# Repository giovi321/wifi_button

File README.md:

This is a cheap, customizable, WiFi-enabled, battery-operated, ultra-low power consumption touch button with no moving parts that relies on ESPHome and is designed to be used with Home Assistant.
It is designed to be long-lasting both in terms of durability and battery life and easy to build & operate.

Did you like the project?

# License
The content of this repository is licensed under the [WTFPL](http://www.wtfpl.net/).

```
Copyright © 2023 giovi321
This work is free. You can redistribute it and/or modify it under the
terms of the Do What The Fuck You Want To Public License, Version 2,
as published by Sam Hocevar. See the LICENSE file for more details.
```

# Features
- Minimalist design (i.e., no moving parts, fit with the design of my house)
- No mechanical button (i.e., I just want to slap my hand on a big enough device while I'm laying on my bed)
- USB type C charging port (i.e., charge it with my laptop charger)
- At least one year of battery (i.e., charge it once a year and forget about it)
- WiFi enabled, I don't want to configure also BLE on my Home Assistant device
- Battery status (i.e., get a notification on Home Assistant when it needs to be charged)
- As cheap as possible (this makes z-wave not an option)

# Shopping list
The items in the following links are just proposals, you can obviously source the exact same products wherever you prefer.
Prices include shipping to Europe.
- [Wemos D1 Mini](https://www.aliexpress.com/item/32651747570.html) [3.33€]
- [USB plug](https://www.aliexpress.com/item/1005005476223469.html) [1.77€]
- [USB type C charging circuit](https://www.aliexpress.com/item/1005005227218470.html) [1.87€]
- [Battery 2000mAh](https://www.aliexpress.com/item/1005002919536938.html) [5.44€]
- [Photocoupler TLP570](https://www.aliexpress.com/item/1005004627959174.html) [2.14€]
- [Capacitive touch sensor](https://www.aliexpress.com/item/32874585710.html) [0.60€]
- [180k ohm resistor](https://aliexpress.com/item/1005004562905294.html) [2.55€]
- [Autotapping screws M2.6 x 5mm](https://www.aliexpress.com/item/1005003330377202.html)  [1.30€]
- Optional: [Screw connector for PCB](https://www.aliexpress.com/item/4001283309384.html), if you want you can solder the battery directly to the PCB/breadboard [1.90€]
- Optional: [PCB pin header strip](https://www.aliexpress.com/item/1005003541838313.html), if you want you can solder the cables that connect the touch sensor directly to the PCB/breadboard [1.17€]
- Optional: [PCB mounted micro switch 90°](https://www.aliexpress.com/item/1005005338134247.html), if you don't require the switch, you can place a jumper in place of the switch in the board [3.15€]

- Options for PCB:
  - Breadbord (make your own design) [c. 3€]
  - PCB I have designed
    - Available for purchase [here](https://www.buymeacoffee.com/giovi321/e/147823) [15€ cad., 3€ for additional boards]
    - Print your own on [allpcb](https://www.allpcb.com/?Mb_InviteId=60399) [c. 30€ excl. import taxes], see the Gerber files in the repository
 - 3D printed case (see the .stl files in this repository)
   -  Print it yourself [c. 3€]
   -  Print it on xometry.eu [c. 36€]

# Resources
- Circuit schematic - see the files in the "PCB" folder of the repository

- 3D case - see the files in the "3D stl" folder of the repository and check the README.md file in that folder

# How does it work
- The USB type C connector makes the device modern and easy to charge, but feel free to use any other type of connector
- The charger module keeps the battery charged and you safe from fire hazards, it is simply plug and play
- The device is based on the Wemos D1 Mini (I'm using a cheap clone, even though a branded one would be better for lower energy consumption) and ESPHome because they are very easy to use; certainly there are more energy efficient solutions
- We need a voltage sensor connected to one analog input of the Wemos D1 Mini in order to read the battery status and receive a notification on Home Assistant when it is about to die. To do this, we take advantage of the integrated voltage divider of the pin A0 of the Wemos D1 Mini, which can support up to 3.3 volts input. Since we are providing a 5 volts input, we need to add a 180kohm resistor
- In order to keep energy consumption low, we need to keep the Wemos D1 Mini in a deep-sleep state
	- however, in deep sleep state the Wemos D1 Mini won't be able to read an input offered by the touch sensor
	- therefore, I have opted to use the touch sensor to wake up the Wemos D1 Mini that will go in deep-sleep automatically every 10 seconds
	- the Wemos D1 Mini will be configured to send two mqtt messages whenever it wakes up:
		- one message with the battery voltage
		- one message with "hey somebody touched the touch sensor"
- 3.7v battery is the way to go to power the Wemos D1 Mini, and 2000 mAh fits the small design of the case; feel free to use a different amperage battery. It provides up to 1.5 years of uptime on a single charge (it can vary, see the dedicated section of this file)
   - I haven't tested it, but from my research online the power consumption of different versions of Wemos D1 Mini in deep-sleep mode powered from the 5v input (which is less efficient because there is a voltage regulator in the middle) can vary depending on the manufacturer (see table below)
   - Assuming we are unlucky and got the worse energy-performing Wemos D1 Mini, the average consumption is 69.47mA, giving it a life of almost 399 days (the calculation steps are available below). If we take into consideration the best case scenario, that is 78µA consumption, the battery would last almost 3x: 1,068 days
   - We are not taking into consideration the power consumption of the touch sensor, phototransistor and voltage sensor. The first two components have a very small consumption as it peaks mostly when you activate the touch sensor. For the voltage sensor I couldn't find anything online. In any case, even assuming an absurde value of 15% increase in power consumption, it's still a decent number of days.
   - I don't think I need to say that: i) these values are purely theorethical, the nominal rating of the battery does not equal its empirical performance; ii) the amount of times you will use the button will influence the duration of the battery
   - Pro tip: if you desolder the LED that is installed on the touch sensor, you save some precious µA. However I haven't tried it and I don't know if it would affect the touch sensor functionality
```
Wemos D1 Mini power consumption table
          | WEMOS D1 MINI CLONE | WEMOS D1 MINI LOLIN | WEMOS D1 MINI WAVGAT |
|:-------:|:-------------------:|:-------------------:|:--------------------:|
| Minimum |        144 µA       |         75µA        |        206 µA        |
| Maximum |        147 µA       |         80µA        |        214 µA        |
| Average |        156 µA       |         78µA        |        209 µA        |

Source: https://programarfacil.com/esp8266/esp8266-deep-sleep-nodemcu-wemos-d1-mini/
```
```
Battery life calculation steps
To calculate the approximate duration of a battery with a given load, you can use the formula:
	Battery Life (in hours) = Battery Capacity (in mAh) / (Load Current (in µA) / 1000)
The battery capacity is 2000 mAh and the load current is 209 µA. Plugging these values into the formula:
	Battery Life = 2000 mAh / (209 µA / 1000) ≈ 9569.38 hours
	Battery Life in days = 9569.38 hours / 24 ≈ 398.72 days
```
- As mentioned earlier, a touch sensor does not provide an analog output. To use it, you need to interface it with a microcontroller like the Wemos D1 Mini, or in our case, to minimize energy consumption, we can opt to use a phototransistor
- The phototransistor is a straightforward electronic component with two inputs and two outputs:
	- the two inputs are the anode (+) and cathode (-) of a LED integrated in the package of the chip
	- the two outputs are the Emitter and Collector of the transistor, to put it simple those two pins allow current to flow between the two pins when the phototransistor is "activated"
- When the touch sensor is activated with your finger, it provides the phototransistor with current, enough to light the internal LED of the phototransistor, therefore allowing current to pass between the emitter and the collector of the transistor
  - When the current flows between the Emitter and the Collector, we are simply shorting the RST and GND pins of the Wemos D1 Mini, therefore waking it up

# Building process
## Hardware
### Electronics
Just follow the schematics provided in the Resources chapter of the readme to build your own breadbord, otherwise simply solder the components on the PCB ordered either from me or another producer.

### Case
The assembly is extremly simple:
- Using a flat cutter, trim the pins protruding from the PCB of the touch sensor in order to make in more flat and therefore make sure it sticks closely to the top of the case
- Hot glue the touch sensor to the top flat part of the dome (inside the dome, obviously) - the sensor can feel touch also through a thin layer of non conductive material (the layer of the top of the dome is 1mm thick)
- Insert the USB type C connector from the bottom of the bottom plate and glue it with cyanoacrylate glue
- Solder the connector to the battery charger module and plug the battery
- Place the PCB on the stands of the bottom part of the case (if you wish, you can melt with a hot flat-head screwdriver the plastic to keep the PCB in place)
- Close the dome and use four M2.6 screws to secure it

## Software
### Install ESPHome
There are three ways to install ESPHome:
- If you have hass.io (the official home-assistant OS), follow [this guide](https://www.home-assistant.io/integrations/esphome/)
- If you are running any other version of home-assistant such as a venv or docker you have the following two options:
  - Use docker, following [this guide](https://esphome.io/guides/installing_esphome.html)
  - Install it in a python venv following the simple steps below or follow [this guide](https://esphome.io/guides/installing_esphome.html)
```
python3 -m venv esphome
source esphome/bin/activate
pip3 install esphome
```
Check that ESPHome has been installed correctly:
```
esphome version
```
If you're not running hass.io, you can install ESPHome dashboard by following the steps below or [this guide](https://esphome.io/guides/getting_started_command_line.html?highlight=dashboard+install#bonus-esphome-dashboard)

```esphome dashboard config/
pip install tornado esptool
```
Test the installation:`esphome dashboard config/`
Create a new systemd service to run the dashboard automatically by issuing (as root) `nano /etc/systemd/system/esphome.service`.
Now put this in the file, close and save it.
```
[Unit]
Description=ESPHome Dashboard
After=network-online.target

[Service]
Type=simple
ExecStart=/root/esphome/bin/esphome config/ dashboard
Restart=on-failure
RestartSec=5s

[Install]
WantedBy=multi-user.target
```
Issue the following:
```
systemctl --system daemon-reload
systemctl enable esphome.service
```
Then check if the service is running by issuing `service esphome status`.

### ESPHome code
ATTENTION: remember to switch off the main circuit board (or unplug the battery, if you didn't include the switch) before connecting the Wemos D1 Mini to the computer via USB!

```
mqtt:
  broker: 192.168.1.100
  username: yourmqttusername
  password: yourmqttpassword
  birth_message:
    topic: esphome/bedside_light_switch_1
    payload: "on"

deep_sleep:
  run_duration: 10s

sensor:
  - platform: adc
    pin: A0
    name: "Bedside light switch 1 battery"
    id: battery_voltage_12f
    filters:
      - multiply: 4.511904762
    accuracy_decimals: 3
```
ATTENTION: to calculate the 4.511904762 value (second line from the bottom of the code snippet for ESPHome) you need to:
- measure the battery voltage with a multimeter when the device is running (i.e., not in deep-sleep mode)
- set the value to 1 like this: `multiply: 1`
- check what value is reported on home assistant from the device
- do a very simple proportion:
```
a:b=c:x
b*c/a=x
a=the reported voltage from home assistant
b=the multiplier you set (1)
c=the voltage measured by your multimeter

0.840:1=3.79:x
1*3.79/0.840=4.511904762
```
So with those numbers (they might vary depending on the Wemos D1 Mini brand and the battery type) the multiplier we need to set is 4.511904762.

### Home Assistant code
Add the sensor for the battery to convert voltage to percentage (edit configuration.yaml)
Remember to change the name of the sensor `sensor.bedside_light_button_1_bedside_light_button_1_battery` to your sensor's name.
The values shown in this code snipped apply to 3.7v lithium batteries.
```
sensor:
  - platform: template
    sensors:
      bedside_light_button_1_battery_percentage:
        friendly_name: "Bedside light button 1 battery percentage"
        device_class: battery
        unit_of_measurement: "%"
        value_template: >
          {% set voltage = states('sensor.bedside_light_button_1_bedside_light_button_1_battery')|float %}
          {% if voltage < 2.64 %}
            0
          {% else %}
            {% set range_voltage = 3.85 - 2.64 %}
            {% set range_percentage = 100 %}
            {% set battery_percentage = ((voltage - 2.64) / range_voltage) * range_percentage %}
            {{ battery_percentage | round(0) }}
          {% endif %}
```

Add the automation to trigger the light when you press the button (edit automations.yaml):
```
- alias: bedside_light_switch_1
  description: 'Turn on bedside table lamp on button touch'
  trigger:
  - platform: mqtt
    topic: esphome/bedside_light_switch_1
    payload: 'on'
  mode: single
```

Add  a notification on low battery (edit automations.yaml):
```
- alias: Bedside light 1 low battery
  description: 'Send notification if bedside light button battery is below 10%'
  trigger:
  - platform: numeric_state
    entity_id: sensor.bedside_light_button_1_battery
    below: 10
  action:
  - service: notify.persistent_notification
    data:
      message: The battery of bedside light 1 is low. Please charge.
      title: Bedside light 1 low battery
  mode: single
```

# The outcome
The final result:
[Piucture TBU]

The bare metal device:

The early prototype:

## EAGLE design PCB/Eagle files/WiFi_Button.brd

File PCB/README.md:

In this folder you can find all the files needed to print the PCB.
If you need to print from [allpcb](https://www.allpcb.com/?Mb_InviteId=60399), simply upload the file WiFi_Button.zip.

## Schematic

## PCB layout

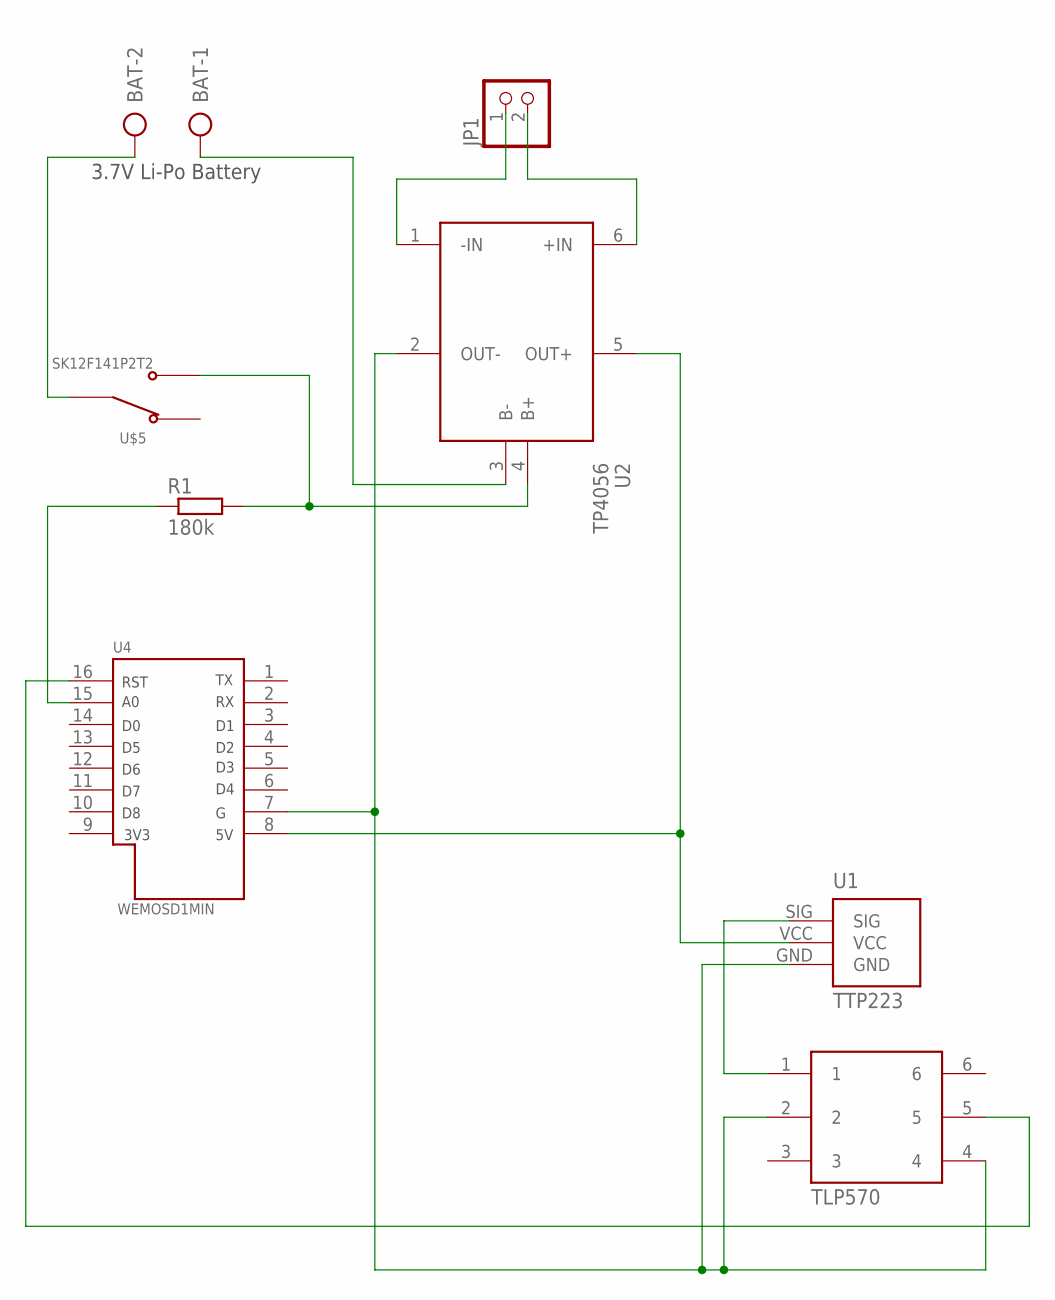
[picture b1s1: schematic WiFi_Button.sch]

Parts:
BAT: AK500/2
JP1: PINHD-1X2; 1X02
R1: 180k; 0207/10
U1: TTP223
U2: TP4056
U3: TLP570; DIL06
U4: WEMOSD1MIN
U$5: SK12F141P2T2

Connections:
unnamed: BAT.2, U$5.2
unnamed: R1.2, U2.4 (B+), U$5.3
unnamed: BAT.1, U2.3 (B-)
unnamed: U1.VCC, U2.5 (OUT+), U4.8 (5V)
unnamed: U1.GND, U2.2 (OUT-), U3.2, U3.4, U4.7 (G)
unnamed: U1.SIG, U3.1
unnamed: U3.5, U4.16 (RST)
unnamed: JP1.1, U2.1 (-IN)
unnamed: JP1.2, U2.6 (+IN)
unnamed: R1.1, U4.15 (A0)

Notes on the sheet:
3.7V Li-Po Battery

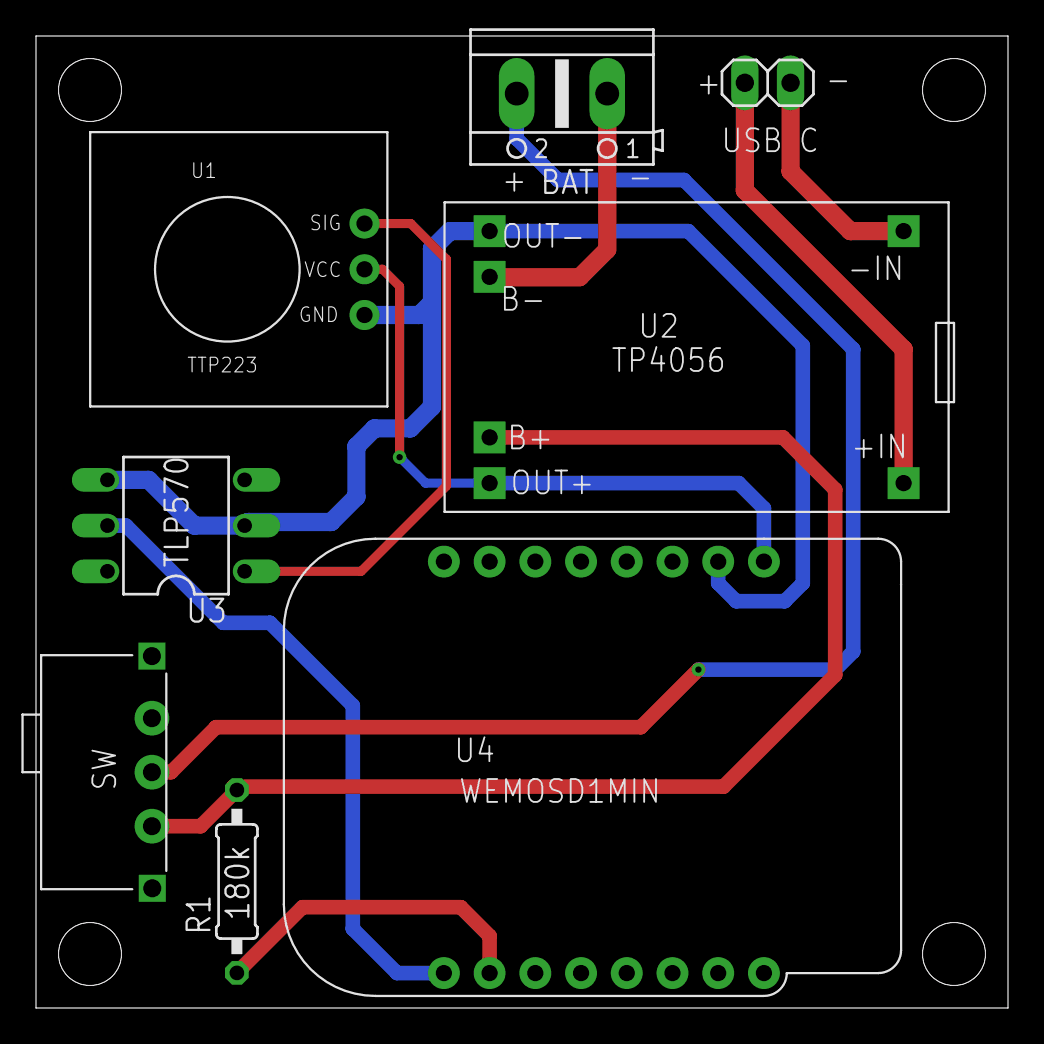
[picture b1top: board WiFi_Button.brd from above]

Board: 2 copper layers, 54.0 x 54.0 mm, 8 parts (0 on the bottom side), 10 nets.

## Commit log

2023-06-08 Update LICENSE
